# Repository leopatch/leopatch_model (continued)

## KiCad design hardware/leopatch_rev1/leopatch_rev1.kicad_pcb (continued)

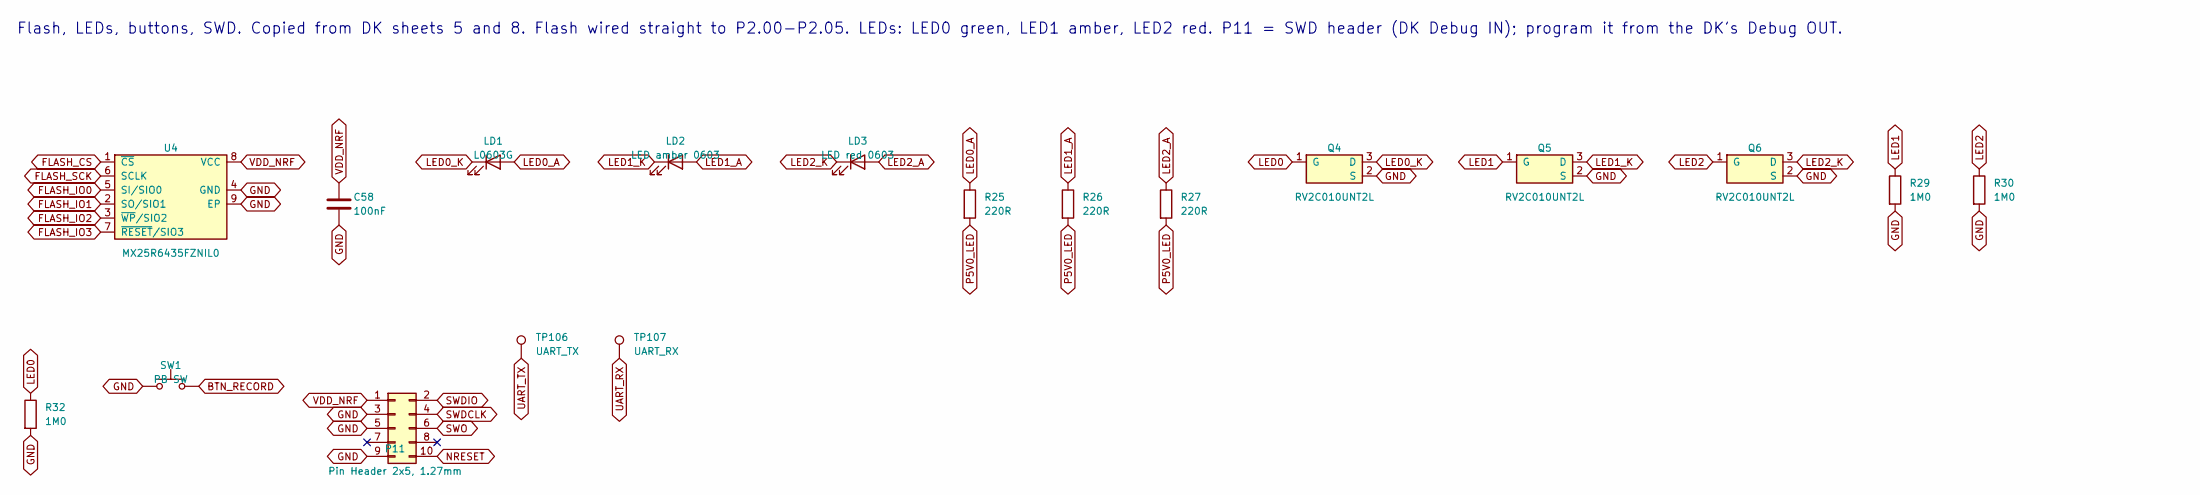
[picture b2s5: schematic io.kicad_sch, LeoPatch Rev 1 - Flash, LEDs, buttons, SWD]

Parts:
C58: 100nF; CAPC0603X03L_C; MPN N.A.
LD1: L0603G; LED_0603_G; MPN VS 25C7M5
LD2: LED amber 0603; LED_0603_G
LD3: LED red 0603; LED_0603_G
P11: Pin Header 2x5, 1.27mm; HDR_2x5-SMD-1.27mm-K; MPN 3132-10MS0BK00R5
Q4, Q5, Q6: RV2C010UNT2L; DFN65P100X40-3L; MPN RV2C010UNT2L
R25, R26, R27: 220R; RESC0603X03L_C; MPN N.A.
R29, R30, R32: 1M0; RESC0603X03L_C; MPN N.A.
SW1: PB SW; Switch-PB-6.2x6.3mm-SMD; MPN TS604VM1-025BR-R
TP106: UART_TX; TP_SMD_D1.5mm
TP107: UART_RX; TP_SMD_D1.5mm
U4: MX25R6435FZNIL0; SON127P600X80_HS-9N; MPN MX25R6435FZNIL0

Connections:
BTN_RECORD: SW1.2; also elsewhere on the board
FLASH_CS: U4.1 (~CS); also elsewhere on the board
FLASH_IO0: U4.5 (SI/SIO0); also elsewhere on the board
FLASH_IO1: U4.2 (SO/SIO1); also elsewhere on the board
FLASH_IO2: U4.3 (~WP/SIO2); also elsewhere on the board
FLASH_IO3: U4.7 (~RESET/SIO3); also elsewhere on the board
FLASH_SCK: U4.6 (SCLK); also elsewhere on the board
GND: C58.2, P11.3, P11.5, P11.9, Q4.2 (S), Q5.2 (S), Q6.2 (S), R29.2, R30.2, R32.2, SW1.1, U4.4 (GND), U4.9 (EP); also elsewhere on the board
LED0: Q4.1 (G), R32.1; also elsewhere on the board
LED0_A: LD1.2 (A), R25.1
LED0_K: LD1.1 (K), Q4.3 (D)
LED1: Q5.1 (G), R29.1; also elsewhere on the board
LED1_A: LD2.2 (A), R26.1
LED1_K: LD2.1 (K), Q5.3 (D)
LED2: Q6.1 (G), R30.1; also elsewhere on the board
LED2_A: LD3.2 (A), R27.1
LED2_K: LD3.1 (K), Q6.3 (D)
NRESET: P11.10; also elsewhere on the board
P5V0_LED: R25.2, R26.2, R27.2; also elsewhere on the board
SWDCLK: P11.4; also elsewhere on the board
SWDIO: P11.2; also elsewhere on the board
SWO: P11.6; also elsewhere on the board
UART_RX: TP107.1; also elsewhere on the board
UART_TX: TP106.1; also elsewhere on the board
VDD_NRF: C58.1, P11.1, U4.8 (VCC); also elsewhere on the board

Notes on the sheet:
Flash, LEDs, buttons, SWD. Copied from DK sheets 5 and 8. Flash wired straight to P2.00-P2.05. LEDs: LED0 green, LED1 amber, LED2 red. P11 = SWD header (DK Debug IN); program it from the DK's Debug OUT.

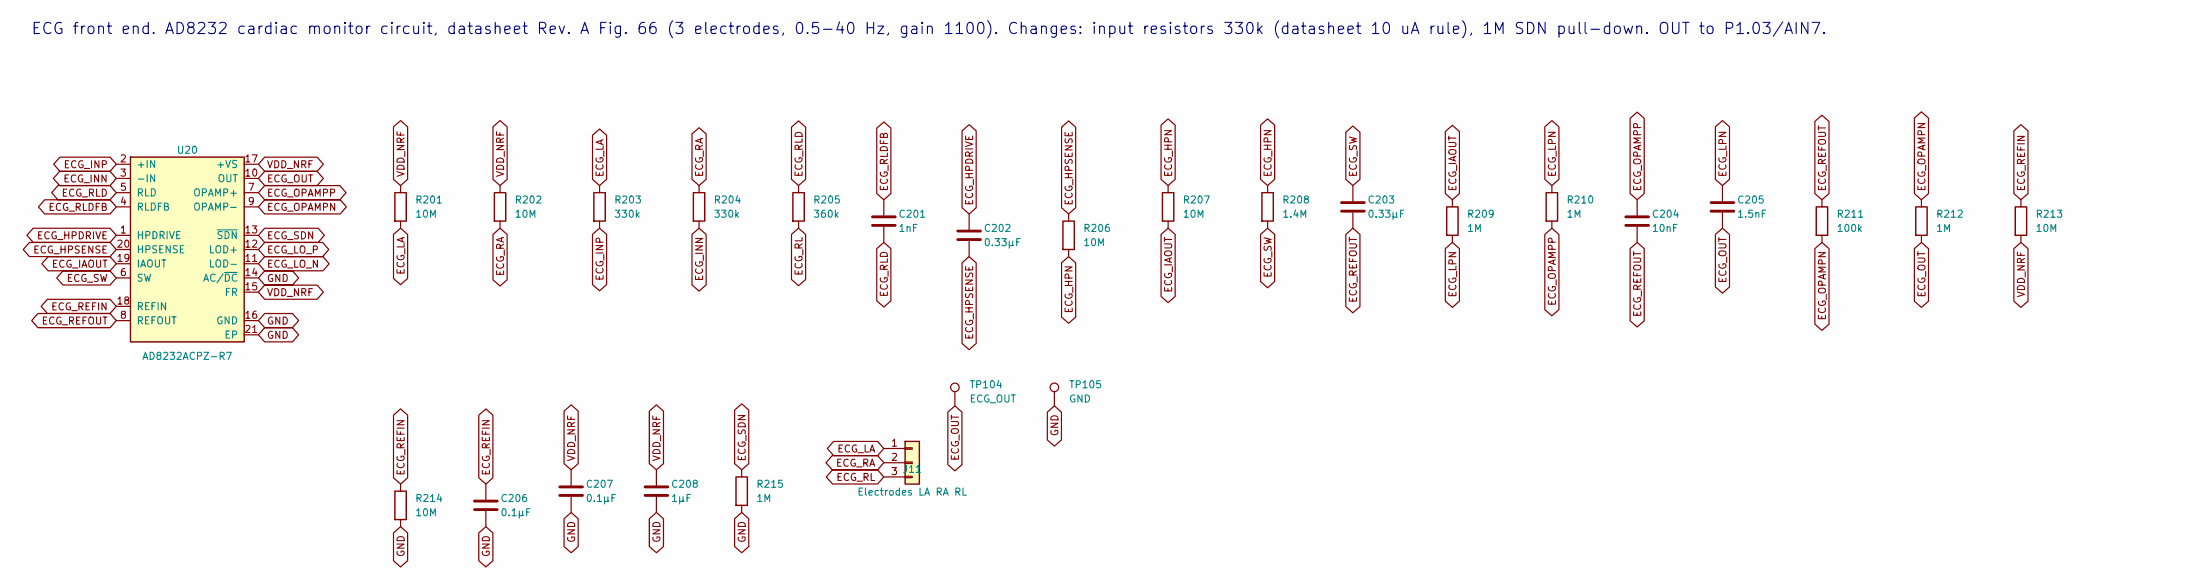
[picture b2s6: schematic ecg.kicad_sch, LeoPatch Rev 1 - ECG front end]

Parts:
C201: 1nF; CAPC1005X04L
C202, C203: 0.33µF; CAPC1005X04L
C204: 10nF; CAPC1005X04L
C205: 1.5nF; CAPC1005X04L
C206, C207: 0.1µF; CAPC1005X04L
C208: 1µF; CAPC1005X04L
J11: Electrodes LA RA RL; JST_PH_B3B-PH-K_1x03_P2.00mm_Vertical; MPN B3B-PH-K-S
R201, R202, R206, R207, R213, R214: 10M; RESC1005X04L
R203, R204: 330k; RESC1005X04L
R205: 360k; RESC1005X04L
R208: 1.4M; RESC1005X04L
R209, R210, R212, R215: 1M; RESC1005X04L
R211: 100k; RESC1005X04L
TP104: ECG_OUT; TP_SMD_D1.5mm
TP105: GND; TP_SMD_D1.5mm
U20: AD8232ACPZ-R7; LFCSP-20-1EP_4x4mm_P0.5mm_EP2.5x2.5mm; MPN AD8232ACPZ-R7

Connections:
ECG_HPDRIVE: C202.1, U20.1 (HPDRIVE)
ECG_HPN: R206.2, R207.1, R208.1
ECG_HPSENSE: C202.2, R206.1, U20.20 (HPSENSE)
ECG_IAOUT: R207.2, R209.1, U20.19 (IAOUT)
ECG_INN: R204.2, U20.3 (-IN)
ECG_INP: R203.2, U20.2 (+IN)
ECG_LA: J11.1, R201.2, R203.1
ECG_LO_N: U20.11 (LOD-); also elsewhere on the board
ECG_LO_P: U20.12 (LOD+); also elsewhere on the board
ECG_LPN: C205.1, R209.2, R210.1
ECG_OPAMPN: R211.2, R212.1, U20.9 (OPAMP-)
ECG_OPAMPP: C204.1, R210.2, U20.7 (OPAMP+)
ECG_OUT: C205.2, R212.2, TP104.1, U20.10 (OUT); also elsewhere on the board
ECG_RA: J11.2, R202.2, R204.1
ECG_REFIN: C206.1, R213.1, R214.1, U20.18 (REFIN)
ECG_REFOUT: C203.2, C204.2, R211.1, U20.8 (REFOUT)
ECG_RL: J11.3, R205.2
ECG_RLD: C201.2, R205.1, U20.5 (RLD)
ECG_RLDFB: C201.1, U20.4 (RLDFB)
ECG_SDN: R215.1, U20.13 (~SDN); also elsewhere on the board
ECG_SW: C203.1, R208.2, U20.6 (SW)
GND: C206.2, C207.2, C208.2, R214.2, R215.2, TP105.1, U20.14 (AC/~DC), U20.16 (GND), U20.21 (EP); also elsewhere on the board
VDD_NRF: C207.1, C208.1, R201.1, R202.1, R213.2, U20.15 (FR), U20.17 (+VS); also elsewhere on the board

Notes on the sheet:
ECG front end. AD8232 cardiac monitor circuit, datasheet Rev. A Fig. 66 (3 electrodes, 0.5-40 Hz, gain 1100). Changes: input resistors 330k (datasheet 10 uA rule), 1M SDN pull-down. OUT to P1.03/AIN7.

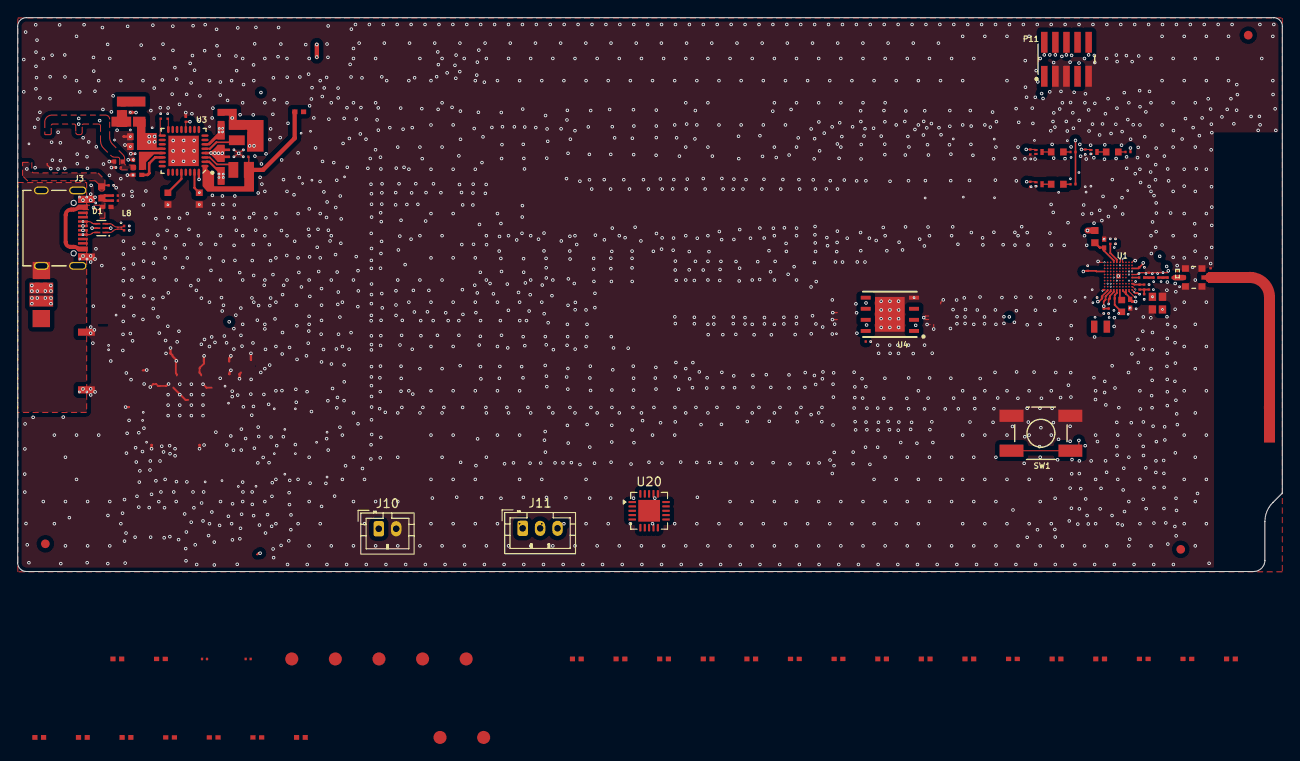
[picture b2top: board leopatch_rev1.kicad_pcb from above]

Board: 8 copper layers, 145.0 x 63.5 mm, 120 parts (0 on the bottom side), 90 nets.

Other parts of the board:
Fid1, Fid2, Fid3: Fiducial mark; Fiducial

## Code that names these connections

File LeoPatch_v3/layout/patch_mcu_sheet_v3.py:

"""LeoPatch v3: module pins for the MAX30003 SPI on the MCU sheet, and TP3 (ECG_OUT) removed.
Run with system python3 from the LeoPatch_v3 folder, with KiCad closed."""
import re, uuid
U = lambda: str(uuid.uuid4())
t = open("LeoPatch_MCU.kicad_sch").read()
assert "ECG_SCK" not in t, "already patched"


def block(s, start):
    d = 0
    for j in range(start, len(s)):
        if s[j] == "(": d += 1
        elif s[j] == ")":
            d -= 1
            if d == 0: return s[start:j + 1]


# left-side module pins: K8 -> ECG_MOSI, C9 -> ECG_INT, D9 -> ECG_CS, E9 -> ECG_SCK (global labels at x = 162.56)
for old, new, y in (("ECG_OUT", "ECG_MOSI", 116.84), ("ECG_LO+", "ECG_INT", 111.76), ("ECG_LO-", "ECG_CS", 114.3), ("ECG_SDN", "ECG_SCK", 119.38)):
    a = f'(global_label "{old}"\n\t\t(shape bidirectional)\n\t\t(at 162.56 {y:g} 180)'
    assert t.count(a) == 1, old
    t = t.replace(a, a.replace(old, new))
# A8 (P1.02) -> ECG_MISO: replace its no-connect flag with a global label
m = re.search(r'\t\(no_connect\n\t\t\(at 215\.9 119\.38\)\n\t\t\(uuid "[^"]+"\)\n\t\)\n', t)
assert m, "A8 no-connect not found"
t = t[:m.start()] + t[m.end():]
lbl = ('\t(global_label "ECG_MISO"\n\t\t(shape bidirectional)\n\t\t(at 215.9 119.38 0)\n\t\t(effects\n\t\t\t(font\n\t\t\t\t(size 1.27 1.27)\n\t\t\t)\n'
       f'\t\t\t(justify left)\n\t\t)\n\t\t(uuid "{U()}")\n\t)\n')
# TP3 and its ECG_OUT label go
i = t.index('(reference "TP3")'); k = t.rindex("\t(symbol\n", 0, i) + 1
t = t.replace(block(t, k) + "\n", "", 1)
a = t.index('(global_label "ECG_OUT"\n\t\t(shape bidirectional)\n\t\t(at 355.6 121.92 270)')
t = t.replace(block(t, a) + "\n", "", 1)
t = t.replace("Test points (1 mm pads on the top side)", "Test points (1 mm pads on the top side): GND and 3V3")
k = t.rindex("\t(sheet_instances") if "\t(sheet_instances" in t else t.rindex("\t(embedded_fonts")
t = t[:k] + lbl + t[k:]
open("LeoPatch_MCU.kicad_sch", "w").write(t)
print("ok")

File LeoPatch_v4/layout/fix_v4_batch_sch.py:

"""LeoPatch v4 schematic batch (system python3, KiCad closed, run from LeoPatch_v4). Then run layout/set_part_fields.py.

MAX30003 sheet, matched to the MAX30003WING2 evaluation kit:
  R201/R202 1k -> 49.9k, C201 10nF -> 1nF, C213/C214 1nF -> 10pF, C202 10uF -> 1uF (0.5 Hz, settles in ~1-2 s),
  new R208 499k from VCM to the RL electrode (eval kit R6)
AD8232 sheet (AD8232 datasheet):
  R603/R604 180k -> 360k (patient current < 10 uA: R >= 3.3 V / 10 uA), output RC to the ADC (Fig. 61):
  U601 OUT is now local net AOUT (TP601 stays on it) -> R623 1k -> ECG_OUT -> C608 10nF to GND -> module pad F7
Status LEDs (active high, GPIO -> R -> LED -> GND):
  D103 PWR (green, R106 1k from +3V3, Power sheet)
  D201 MAX30003 LEADS (green, R206 100R) <- LED_MAX_LEADS, module A7 (P3.03): firmware lights it while DCLOFFINT is clear.
       A7 was ECG_SDN: the AD8232 SDN pin now only has its 10k pull-up R615, so the AD8232 is always on (~170 uA).
       A5 can no longer be routed out of the module.
  D601 AD8232 LEADS (green, R621 100R) <- LED_AD_LEADS, module F8 (P1.17): firmware lights it while LO+ and LO- are low
  (BEAT LEDs were dropped: only three module pins can still be routed out and the board would not route with four LEDs)
"""
import re, sys, uuid
sys.path.insert(0, "layout")
import build_ecg_sheet as B

ROOT = "7a41c3d9-2e65-4f0b-9c88-3d5e1f6a2b90"
SHEETS = {"LeoPatch_ECG.kicad_sch": "f0d23f52-e0d2-5d2d-be47-e1184c1697c7",
          "LeoPatch_ECG_AD8232.kicad_sch": "1d6c4f87-bd9a-573e-bd57-1bf4989b18b5",
          "LeoPatch_Power.kicad_sch": "1bd637cf-7783-5fe2-bdf0-ffd80b334887"}
NS = uuid.UUID("5b0e1c1e-0000-4000-8000-00000000c006")
NEW = ("R208", "D201", "R206", "D601", "R621", "R623", "C608", "D103", "R106")
for r in NEW:
    B.SYM_UUID[r] = str(uuid.uuid5(NS, r))
MCU_PINS = {"F8": "LED_AD_LEADS"}
U = lambda: str(uuid.uuid4())
ui = open("LeoPatch_UI.kicad_sch").read()


def block(s, start):
    d = 0
    for j in range(start, len(s)):
        if s[j] == "(": d += 1
        elif s[j] == ")":
            d -= 1
            if d == 0: return s[start:j + 1]


LED_LIB = block(ui, ui.index('(symbol "Device:LED"'))


def set_value(t, ref, val):
    i = t.index(f'(reference "{ref}")')
    k = t.rindex("(symbol\n\t\t(lib_id", 0, i)
    b = block(t, k)
    nb, c = re.subn(r'(\(property "Value" )"[^"]*"', lambda m: f'{m.group(1)}"{val}"', b, 1)
    assert c == 1, ref
    return t.replace(b, nb, 1)


def led(ref, val, x, y, anode_label):
    s = B.symbol("Device:LED", ref, val, x, y, [("Footprint", "LED_SMD:LED_0603_1608Metric"), ("Datasheet", "~"),
                 ("Description", "Light emitting diode")], ["1", "2"], refxy=(x, y - 3.81), valxy=(x, y + 3.81))
    return s + B.label(anode_label, x + 3.81, y, 0) + B.power("GND", x - 3.81, y)


def led_circuit(ref_r, rval, ref_d, color, x, drive, tag):
    """drive: ('global', NET) or a local label name; R vertical at (x, 76.2), LED horizontal at (x, 92.71)."""
    a = f"LEDA_{tag}"
    return B.passive("R", ref_r, rval, x, 76.2, drive, a) + led(ref_d, color, x, 92.71, a)


def finish(t, body, fname):
    body = body.replace('(project "LeoPatch_v3"', '(project "LeoPatch_v4"')
    if '(symbol "Device:LED"' not in t:
        li = t.index("(lib_symbols") + len("(lib_symbols")
        t = t[:li] + "\n\t\t" + LED_LIB + t[li:]
    k = t.rindex("\t(sheet_instances") if "\t(sheet_instances" in t else t.rindex("\n\t(embedded_fonts") + 1
    t = t[:k] + body + t[k:]
    open(fname, "w").write(t)


# ---------------------------------------------------------------- MAX30003 sheet
f = "LeoPatch_ECG.kicad_sch"
t = open(f).read()
assert '(reference "R208")' not in t, "already applied"
B.PATH = f"/{ROOT}/{SHEETS[f]}"
B.pwr = iter(range(240, 270))
for ref, val in (("R201", "49.9k"), ("R202", "49.9k"), ("C201", "1nF C0G"), ("C213", "10pF C0G"), ("C214", "10pF C0G"), ("C202", "1uF X7R")):
    t = set_value(t, ref, val)
t = t.replace("Input filter (datasheet Figure 11): 1k pulse-proof series resistors, then C201 10 nF across ECGP-ECGN and\\nC213 / C214 1 nF to GND (matched C0G) on the chip side.",
              "Input network as on the MAX30003WING2 evaluation kit: 49.9k pulse-proof series resistors, C201 1 nF across ECGP-ECGN,\\nC213 / C214 10 pF to GND (matched C0G), R208 499k from VCM to the RL electrode. C202 1 uF = 0.5 Hz high-pass.")
body = B.passive("R", "R208", "499k", 266.7, 127.0, "VCM", "RL")
body += led_circuit("R206", "100", "D201", "GREEN", 266.7, ("global", "LED_MAX_LEADS"), "MAXLEADS")
body += B.text("Status LED D201 LEADS: firmware lights it while both electrodes are on (DCLOFFINT clear).", 254.0, 60.96)
finish(t, body, f)

# ---------------------------------------------------------------- AD8232 sheet
f = "LeoPatch_ECG_AD8232.kicad_sch"
t = open(f).read()
B.PATH = f"/{ROOT}/{SHEETS[f]}"
B.pwr = iter(range(640, 670))
for ref in ("R603", "R604"):
    t = set_value(t, ref, "360k")
# SDN is no longer driven by the module: global ECG_SDN -> local SDN (R615 pull-up keeps the AD8232 on)
for m in list(re.finditer(r'\t\(global_label "ECG_SDN"\n', t))[::-1]:          # at U601 SDN and at R615
    b = block(t, m.start() + 1)
    at = re.search(r'\(at ([\d.]+) ([\d.]+) (\d+)\)', b)
    t = t[:m.start() + 1] + B.label("SDN", float(at.group(1)), float(at.group(2)), int(at.group(3))).lstrip("\t").rstrip("\n") + t[m.start() + 1 + len(b):]
assert "ECG_SDN" not in t
n = 0
for m in list(re.finditer(r'\t\(global_label "ECG_OUT"\n', t))[::-1]:
    b = block(t, m.start() + 1)
    at = re.search(r'\(at ([\d.]+) ([\d.]+) (\d+)\)', b)
    t = t[:m.start() + 1] + B.label("AOUT", float(at.group(1)), float(at.group(2)), int(at.group(3))).lstrip("\t").rstrip("\n") + t[m.start() + 1 + len(b):]
    n += 1
assert n == 4, n
body = B.passive("R", "R623", "1k", 304.8, 127.0, "AOUT", ("global", "ECG_OUT"))
body += B.passive("C", "C608", "10nF C0G", 330.2, 127.0, ("global", "ECG_OUT"), "GND")
body += B.text("Output RC to the nRF54 ADC (AD8232 datasheet Fig. 61): the AD8232 op amp is slow (100 kHz GBP), C608 supplies the ADC\\nsampling charge. R603/R604 360k: patient current < 10 uA even in a fault (datasheet: R >= supply / 10 uA).", 294.64, 111.76)
body += led_circuit("R621", "100", "D601", "GREEN", 304.8, ("global", "LED_AD_LEADS"), "ADLEADS")
body += B.text("Status LED D601 LEADS: firmware lights it while LO+ and LO- are both low (both electrodes on).", 294.64, 60.96)
finish(t, body, f)

# ---------------------------------------------------------------- Power sheet
f = "LeoPatch_Power.kicad_sch"
t = open(f).read()
B.PATH = f"/{ROOT}/{SHEETS[f]}"
B.pwr = iter(range(130, 150))
body = B.passive("R", "R106", "1k", 88.9, 185.42, "+3V3", "PWR_A") + led("D103", "GREEN", 101.6, 191.77, "PWR_A")
body += B.text("D103: power LED (on whenever the 3.3 V rail is up, ~0.5 mA)", 76.2, 177.8)
finish(t, body, f)

# ---------------------------------------------------------------- MCU sheet: module pads for the three LED GPIOs
mcu = open("LeoPatch_MCU.kicad_sch").read()
sym = block(mcu, mcu.index('(symbol "LeoPatch:BM20BC"'))
pins = {num: (float(x), float(y), int(a)) for x, y, a, num in
        re.findall(r'\(pin \w+ \w+\s*\(at ([\d.\-]+) ([\d.\-]+) (\d+)\).*?\(number "([^"]*)"', sym, re.S)}
m = re.search(r'\(symbol\s*\(lib_id "LeoPatch:BM20BC"\)\s*\(at ([\d.]+) ([\d.]+) (\d+)\)', mcu)
sx, sy = float(m.group(1)), float(m.group(2))
for pad, netname in MCU_PINS.items():
    x, y, a = pins[pad]
    px, py = round(sx + x, 2), round(sy - y, 2)
    nc = re.search(r'\t\(no_connect\n\t\t\(at %s %s\)\n\t\t\(uuid "[^"]+"\)\n\t\)\n' % (re.escape(f"{px:g}"), re.escape(f"{py:g}")), mcu)
    assert nc, (pad, px, py)
    ang = {0: 180, 180: 0, 90: 270, 270: 90}[a]
    mcu = mcu[:nc.start()] + B.label(netname, px, py, ang, glob=True) + mcu[nc.end():]
    print(pad, netname, px, py)
# A7 (P3.03) was ECG_SDN -> now drives the MAX30003 LEADS LED
assert mcu.count('(global_label "ECG_SDN"') == 1
mcu = mcu.replace('(global_label "ECG_SDN"', '(global_label "LED_MAX_LEADS"')
open("LeoPatch_MCU.kicad_sch", "w").write(mcu)
print("ok")

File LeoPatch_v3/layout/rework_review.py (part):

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rm_via(129.3, 129.1); via(SW, 129.75, 129.5)
path(SW, F, [(129.2, 129.0), (129.75, 129.5)]); path(SW, B, [(129.3, 129.1), (129.75, 129.5)])

# C204 pin 2 (HPSENSE) and R206 pin 1 (FILT): done by hand, move_vias_out_of_pads.py finds no free spot for the second
rm_via(118.4, 132.3); rm_path(B, [(118.4, 132.3), (119.3, 132.3), (120.1, 131.5)])
via(HPS, 118.25, 131.3); path(HPS, F, [(118.2, 132.0), (118.25, 131.3)]); path(HPS, B, [(118.25, 131.3), (119.9, 131.3), (120.1, 131.5)])
FILT = "/ECG front end/FILT"
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

TPY = 126.5
for ref, val, netname, x, label in (("TP3", "ECG_OUT", "ECG_OUT", 141.0, "ECG"), ("TP1", "GND", "GND", 144.0, "GND"),
                                    ("TP2", "3V3", "+3V3", 147.0, "3V3")):
    place("TestPoint.pretty", "TestPoint_Pad_D1.0mm", ref, val, x, TPY, 0, {"1": netname})
    silk(label, x, TPY + 1.5)
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                      (157.1, 119.7), (157.1, 131.2), (153.6, 134.7), (151.9, 134.7)])
via("BTN_START", 151.9, 134.7)
path("BTN_START", F, [(151.9, 134.7), (150.85, 135.75), (SX + 3.98, SY - 2.25)])
path("BTN_START", F, [(SX - 3.98, SY - 2.25), (SX + 3.98, SY - 2.25)], 0.3)      # the two pin-1 pads are not tied inside the part
for dx in (-3.98, 3.98):
    vx = SX + dx + (1.0 if dx > 0 else -1.0)
    via("GND", vx, SY + 3.0); path("GND", F, [(SX + dx, SY + 2.25), (vx, SY + 3.0)], 0.3)
silk("START", SX, 133.0, 1.0)

# ---------------------------------------------------------------- 9. RESET button and ECG gain 200
# Small B3U button below EXPORT. nRESET reaches it on the bottom layer down the right edge from J301 pin 10.
place("Button_Switch_SMD.pretty", "SW_SPST_B3U-1000P", "SW303", "RESET", 163.0, 143.2, 180, {"1": RST, "2": "GND"})
path(RST, B, [(169.1, 130.54), (169.1, 142.0), (167.9, 143.2), (166.0, 143.2)])
via(RST, 166.0, 143.2); path(RST, F, [(166.0, 143.2), (164.7, 143.2)])
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
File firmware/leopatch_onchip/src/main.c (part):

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 * removes mains hum and finds the heartbeats. With RUN_MODEL set it also builds the 800-sample
 * median beat, runs the stem on the CPU and the rest of the model on the NPU, and shows the answer
 * on the LEDs:
 *   LED0 = MODEL_POS_LABEL, LED1 = MODEL_NEG_LABEL, LED2 = running (recording or thinking),
 *   LED3 = error
 * With RUN_MODEL off, the recording is only sent (Button 1) and the model runs on the laptop
 * (tools/ble_receive.py); all LEDs are off when the recording is done.
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static const struct gpio_dt_spec lo_plus = GPIO_DT_SPEC_GET(DT_PATH(zephyr_user), lo_plus_gpios);
static const struct gpio_dt_spec lo_minus = GPIO_DT_SPEC_GET(DT_PATH(zephyr_user), lo_minus_gpios);
/* Active low: "active" means shut down. */
static const struct gpio_dt_spec sdn = GPIO_DT_SPEC_GET(DT_PATH(zephyr_user), sdn_gpios);
static const struct gpio_dt_spec button = GPIO_DT_SPEC_GET(DT_ALIAS(sw0), gpios);
static const struct gpio_dt_spec button_upload = GPIO_DT_SPEC_GET(DT_ALIAS(sw1), gpios);
static const struct gpio_dt_spec led_pos = GPIO_DT_SPEC_GET(DT_ALIAS(led0), gpios);
static const struct gpio_dt_spec led_neg = GPIO_DT_SPEC_GET(DT_ALIAS(led1), gpios);
static const struct gpio_dt_spec led_running = GPIO_DT_SPEC_GET(DT_ALIAS(led2), gpios);
static const struct gpio_dt_spec led_error = GPIO_DT_SPEC_GET(DT_ALIAS(led3), gpios);
static const struct device *const console = DEVICE_DT_GET(DT_CHOSEN(zephyr_console));

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
	err = err ?: gpio_pin_configure_dt(&lo_plus, GPIO_INPUT);
	err = err ?: gpio_pin_configure_dt(&lo_minus, GPIO_INPUT);
	err = err ?: gpio_pin_configure_dt(&sdn, GPIO_OUTPUT_INACTIVE);
	for (int i = 0; i < ARRAY_SIZE(leds); i++) {
		err = err ?: gpio_pin_configure_dt(leds[i], GPIO_OUTPUT_INACTIVE);
	}
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		return 0;
	}
	/* Keep the AD8232 running so its output is settled when a recording starts. */
	gpio_pin_set_dt(&sdn, 0);
	if (!self_test()) {
		show(&led_error);
		printk("# error: NPU self-test failed\n");
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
